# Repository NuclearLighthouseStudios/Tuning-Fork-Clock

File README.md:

# Tuning Fork Clock

This repository contains all the files for the Tuning Fork Clock PCB and 3D printed parts.

The PCB was designed for home etching, so the traces are very wide and
the via dimater has been increased so wires can be soldered in to make connections between the layers.

All external connections are broken out on an edge connector at the top that serves as solder pads for making connections.

The "fork mount" directory contains the CAD and STL files for the tuning fork mounting hardware.  
Two 22mH inductors and a 15x5mm neodymium magnet need to be inserted into the base part of the mount.

The polarity of the inductors is not consistent from the factory, so some experimentation is required to get the best results.  
Usually flipping one inductor or the magnet will result in much better vibration of the fork.

The on-board BNC connector can be connected to a scope to observe the output waveform of the pickup.

Check out the [YouTube video](https://www.youtube.com/watch?v=TgB_1jr5b_c) for more info on how it all works.

Also check out [this repository](https://github.com/NuclearLighthouseStudios/Tuning-Fork-Clock-Firmware) for the firmware.

| Reference                                         | Quantity | Value         | Description                                          |
| :------------------------------------------------ | -------: | ------------: | :--------------------------------------------------- |
| C1 C4 C5 C9 C102 C103 C104 C105 C106 C107         | 10       | 100n          | Generic ceramic capacitor                            |
| C101                                              | 1        | 100µ          | Electrolytic capacitor, 16V                          |
| C2 C3                                             | 2        | 47n           | Generic ceramic capacitor                            |
| D1                                                | 1        | 1N4148        | DO-35 Diode                                          |
| D2 D3 D4                                          | 3        |               | 5mm LED                                              |
| J3                                                | 1        |               | Panel Mount BNC Connector                            |
| Q1 Q2 Q3 Q4 Q5 Q6 Q7                              | 7        | BC547B        | 0.1A Ic, 45V Vce, Small Signal NPN Transistor, TO-92 |
| R1 R7 R12 R13 R14 R15 R16 R17 R18 R19 R25 R26 R27 | 13       | 1k            | Metal film resistor 1%, DIN 0207, Horizontal         |
| R2 R6                                             | 2        | 1M            | Metal film resistor 1%, DIN 0207, Horizontal         |
| R20 R21 R22 R23 R24                               | 5        | 10k           | Metal film resistor 1%, DIN 0207, Vertical           |
| R3                                                | 1        | 4.7k          | Metal film resistor 1%, DIN 0207, Horizontal         |
| R4 R5 R10                                         | 3        | 10k           | Metal film resistor 1%, DIN 0207, Horizontal         |
| R8 R9                                             | 2        | 100k          | Metal film resistor 1%, DIN 0207, Horizontal         |
| SW1                                               | 1        |               | Alps EC12E Rotary Encoder with Switch, Vertical      |
| U1                                                | 1        | NE555P        | Precision Timers, 555 compatible, PDIP-8             |
| U10                                               | 1        | 440Hz         | Tuning Fork in 3D printed mount                      |
| U10                                               | 2        | 22mH          | 11mm diameter inductor                               |
| U10                                               | 1        |               | 15x5mm neodymium rod magnet                          |
| U2                                                | 1        | ATtiny4313-PU | 8-Bit Microcontroller, 20Mhz, 4k Flash, 256b RAM     |
| U3                                                | 1        | 74HC595       | 8−Bit shift register                                 |
| U4 U5 U6 U7 U8                                    | 5        | SC39-11YWA    | 7 Segment Display                                    |
| U9                                                | 1        | L7805         | 5V voltage regulator, TO-220                         |

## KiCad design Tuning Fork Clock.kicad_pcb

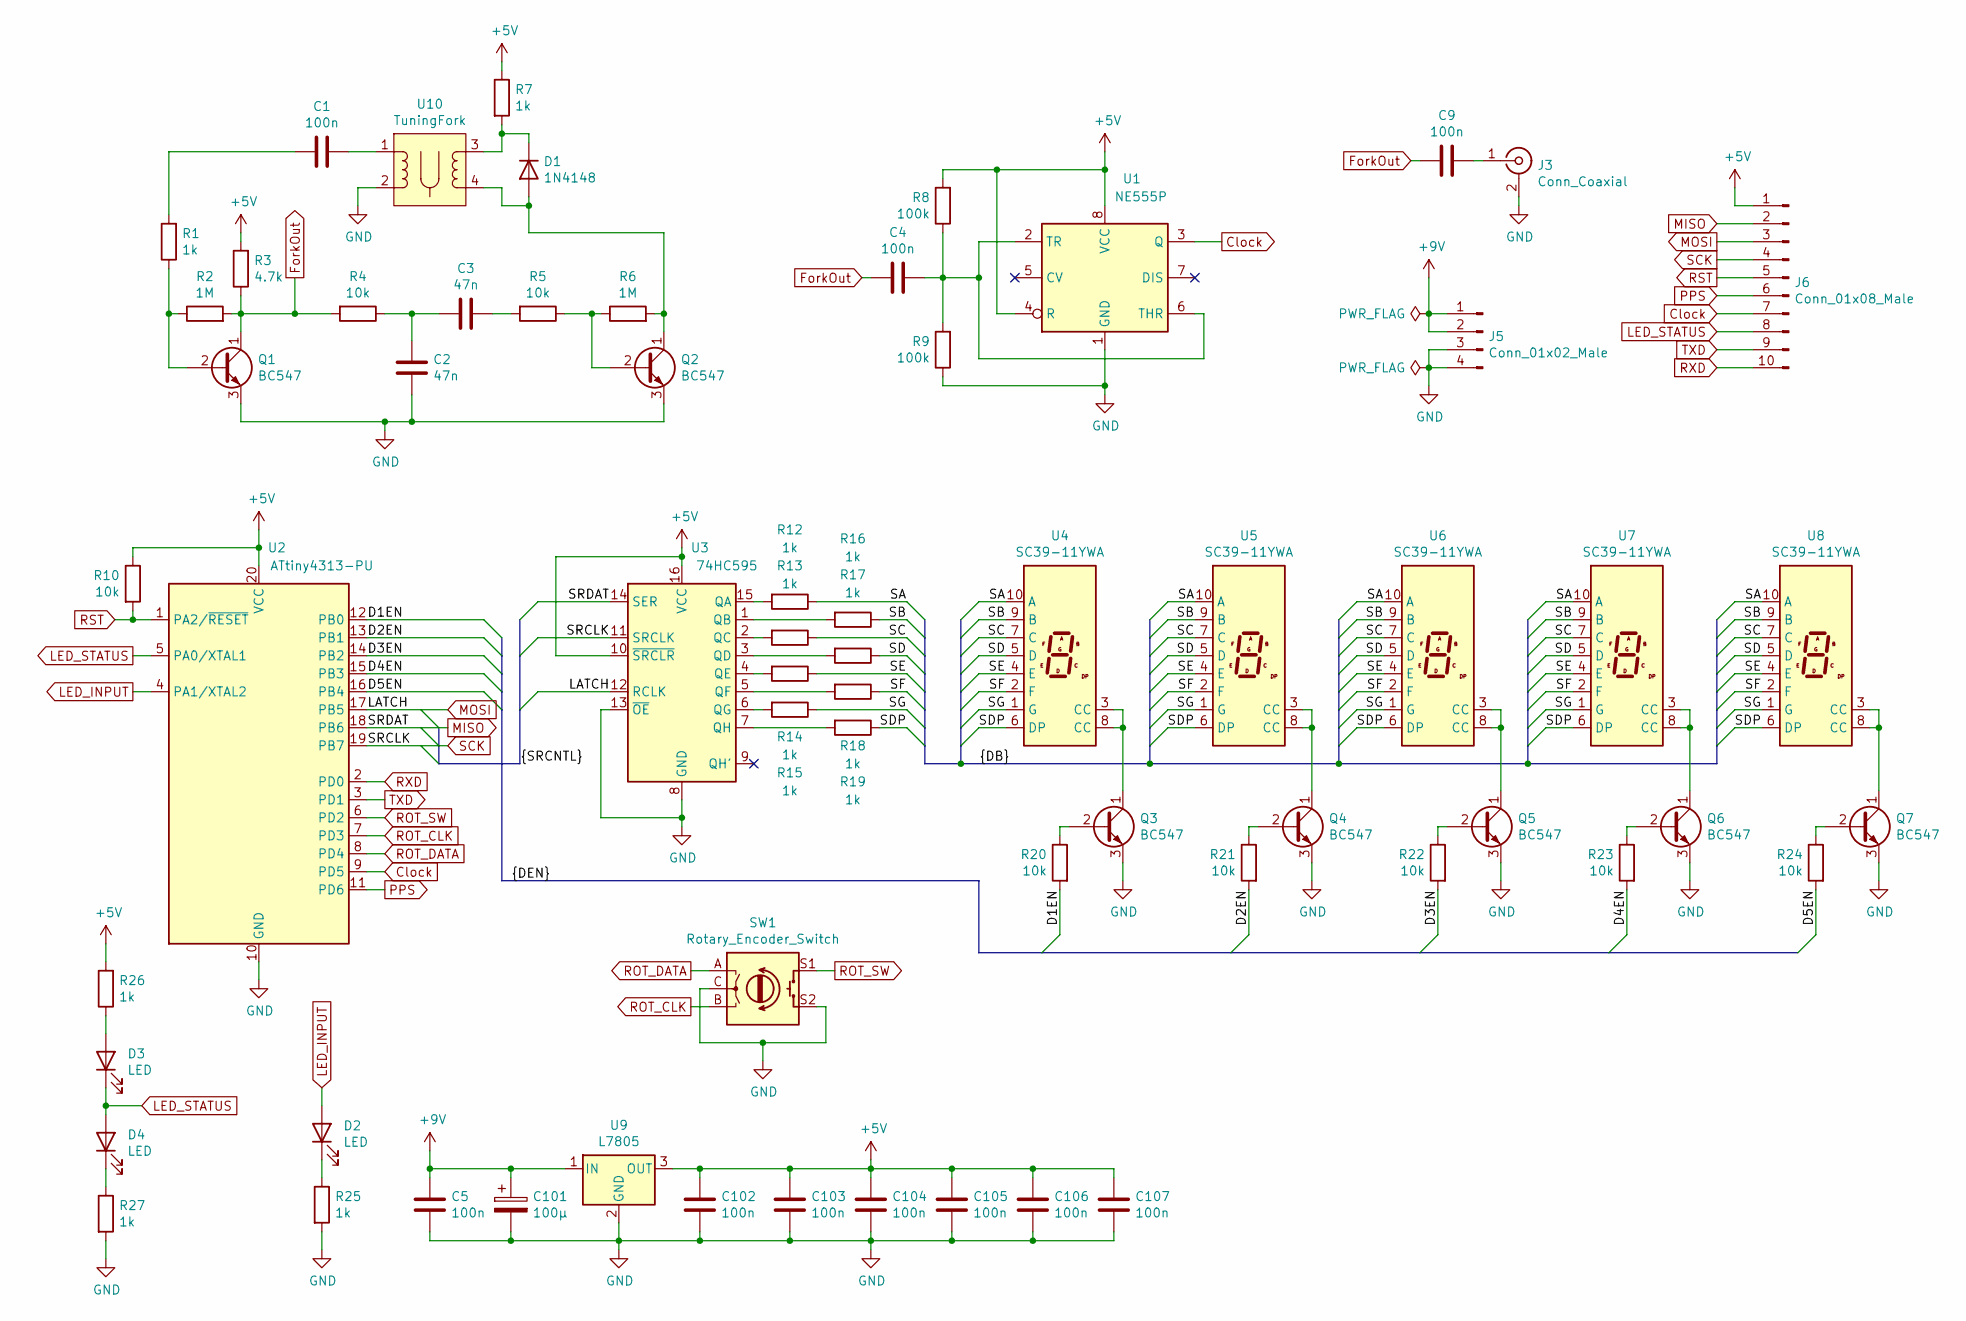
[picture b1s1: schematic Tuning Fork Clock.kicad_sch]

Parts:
C1, C4, C5, C9, C102, C103, C104, C105, C106, C107: 100n; C_Disc_D4.3mm_W1.9mm_P5.00mm
C2, C3: 47n; C_Disc_D4.3mm_W1.9mm_P5.00mm
C101: 100µ; CP_Radial_D6.3mm_P2.50mm
D1: 1N4148; D_DO-35_SOD27_P7.62mm_Horizontal
D2, D3, D4: LED; LED_D5.0mm_Clear
J3: Conn_Coaxial; BNC_PanelMountable_Vertical
J5: Conn_01x02_Male; EdgeConnPower
J6: Conn_01x08_Male; EdgeConnSignal
Q1, Q2, Q3, Q4, Q5, Q6, Q7: BC547; TO-92_Wide
R1, R7, R12, R13, R14, R15, R16, R17, R18, R19, R25, R26, R27: 1k; R_Axial_DIN0207_L6.3mm_D2.5mm_P10.16mm_Horizontal
R2, R6: 1M; R_Axial_DIN0207_L6.3mm_D2.5mm_P10.16mm_Horizontal
R3: 4.7k; R_Axial_DIN0207_L6.3mm_D2.5mm_P10.16mm_Horizontal
R4, R5, R10: 10k; R_Axial_DIN0207_L6.3mm_D2.5mm_P10.16mm_Horizontal
R8, R9: 100k; R_Axial_DIN0207_L6.3mm_D2.5mm_P10.16mm_Horizontal
R20, R21, R22, R23, R24: 10k; R_Axial_DIN0207_L6.3mm_D2.5mm_P2.54mm_Vertical
SW1: Rotary_Encoder_Switch; RotaryEncoder_Alps_EC12E-Switch_Vertical_H20mm_CircularMoun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
U1: NE555P; DIP-8_W7.62mm_Socket
U2: ATtiny4313-PU; DIP-20_W7.62mm_Socket
U3: 74HC595; DIP-16_W7.62mm_Socket
U4, U5, U6, U7, U8: SC39-11YWA; 7SegmentLED_LTS6760_LTS6780
U9: L7805; TO-220-3_Horizontal_TabDown
U10: TuningFork; Tuning Fork

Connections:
+5V: C102.1, C103.1, C104.1, C105.1, C106.1, C107.1, J6.1, R3.2, R7.1, R8.2, R10.1, R26.2, U1.4 (R), U1.8 (VCC), U2.20 (VCC), U3.10 (~SRCLR), U3.16 (VCC), U9.3 (OUT)
+9V: C5.1, C101.1, J5.1, J5.2, U9.1 (IN)
/D1EN: R20.2, U2.12 (PB0)
/D2EN: R21.2, U2.13 (PB1)
/D3EN: R22.2, U2.14 (PB2)
/D4EN: R23.2, U2.15 (PB3)
/D5EN: R24.2, U2.16 (PB4)
/SA: R12.1, U4.10 (A), U5.10 (A), U6.10 (A), U7.10 (A), U8.10 (A)
/SB: R16.1, U4.9 (B), U5.9 (B), U6.9 (B), U7.9 (B), U8.9 (B)
/SC: R13.1, U4.7 (C), U5.7 (C), U6.7 (C), U7.7 (C), U8.7 (C)
/SD: R17.1, U4.5 (D), U5.5 (D), U6.5 (D), U7.5 (D), U8.5 (D)
/SDP: R19.1, U4.6 (DP), U5.6 (DP), U6.6 (DP), U7.6 (DP), U8.6 (DP)
/SE: R14.1, U4.4 (E), U5.4 (E), U6.4 (E), U7.4 (E), U8.4 (E)
/SF: R18.1, U4.2 (F), U5.2 (F), U6.2 (F), U7.2 (F), U8.2 (F)
/SG: R15.1, U4.1 (G), U5.1 (G), U6.1 (G), U7.1 (G), U8.1 (G)
Clock: J6.7, U1.3 (Q), U2.9 (PD5)
ForkOut: C4.2, C9.2, Q1.1 (C), R2.2, R3.1, R4.2
GND: C2.2, C5.2, C101.2, C102.2, C103.2, C104.2, C105.2, C106.2, C107.2, J3.2 (Ext), J5.3, J5.4, Q1.3 (E), Q2.3 (E), Q3.3 (E), Q4.3 (E), Q5.3 (E), Q6.3 (E), Q7.3 (E), R9.1, R25.2, R27.2, SW1.C, SW1.S2, U1.1 (GND), U2.10 (GND), U3.8 (GND), U3.13 (~OE), U9.2 (GND), U10.2
LED_INPUT: D2.2 (A), U2.4 (PA1/XTAL2)
LED_STATUS: D3.1 (K), D4.2 (A), J6.8, U2.5 (PA0/XTAL1)
MISO: J6.2, U2.18 (PB6), U3.14 (SER)
MOSI: J6.3, U2.17 (PB5), U3.12 (RCLK)
unnamed: C1.1, U10.1
unnamed: C1.2, R1.2
unnamed: C2.1, C3.2, R4.1
unnamed: C3.1, R5.2
unnamed: C4.1, R8.1, R9.2, U1.2 (TR), U1.6 (THR)
unnamed: C9.1, J3.1 (In)
unnamed: D1.1 (K), R7.2, U10.3
unnamed: D1.2 (A), Q2.1 (C), R6.2, U10.4
unnamed: D2.1 (K), R25.1
unnamed: D3.2 (A), R26.1
unnamed: D4.1 (K), R27.1
unnamed: Q1.2 (B), R1.1, R2.1
unnamed: Q2.2 (B), R5.1, R6.1
unnamed: Q3.1 (C), U4.3 (CC), U4.8 (CC)
unnamed: Q3.2 (B), R20.1
unnamed: Q4.1 (C), U5.3 (CC), U5.8 (CC)
unnamed: Q4.2 (B), R21.1
unnamed: Q5.1 (C), U6.3 (CC), U6.8 (CC)
unnamed: Q5.2 (B), R22.1
unnamed: Q6.1 (C), U7.3 (CC), U7.8 (CC)
unnamed: Q6.2 (B), R23.1
unnamed: Q7.1 (C), U8.3 (CC), U8.8 (CC)
unnamed: Q7.2 (B), R24.1
unnamed: R12.2, U3.15 (QA)
unnamed: R13.2, U3.2 (QC)
unnamed: R14.2, U3.4 (QE)
unnamed: R15.2, U3.6 (QG)
unnamed: R16.2, U3.1 (QB)
unnamed: R17.2, U3.3 (QD)
unnamed: R18.2, U3.5 (QF)
unnamed: R19.2, U3.7 (QH)
PPS: J6.6, U2.11 (PD6)
ROT_CLK: SW1.B, U2.7 (PD3)
ROT_DATA: SW1.A, U2.8 (PD4)
ROT_SW: SW1.S1, U2.6 (PD2)
RST: J6.5, R10.2, U2.1 (PA2/~RESET)
RXD: J6.10, U2.2 (PD0)
SCK: J6.4, U2.19 (PB7), U3.11 (SRCLK)
TXD: J6.9, U2.3 (PD1)

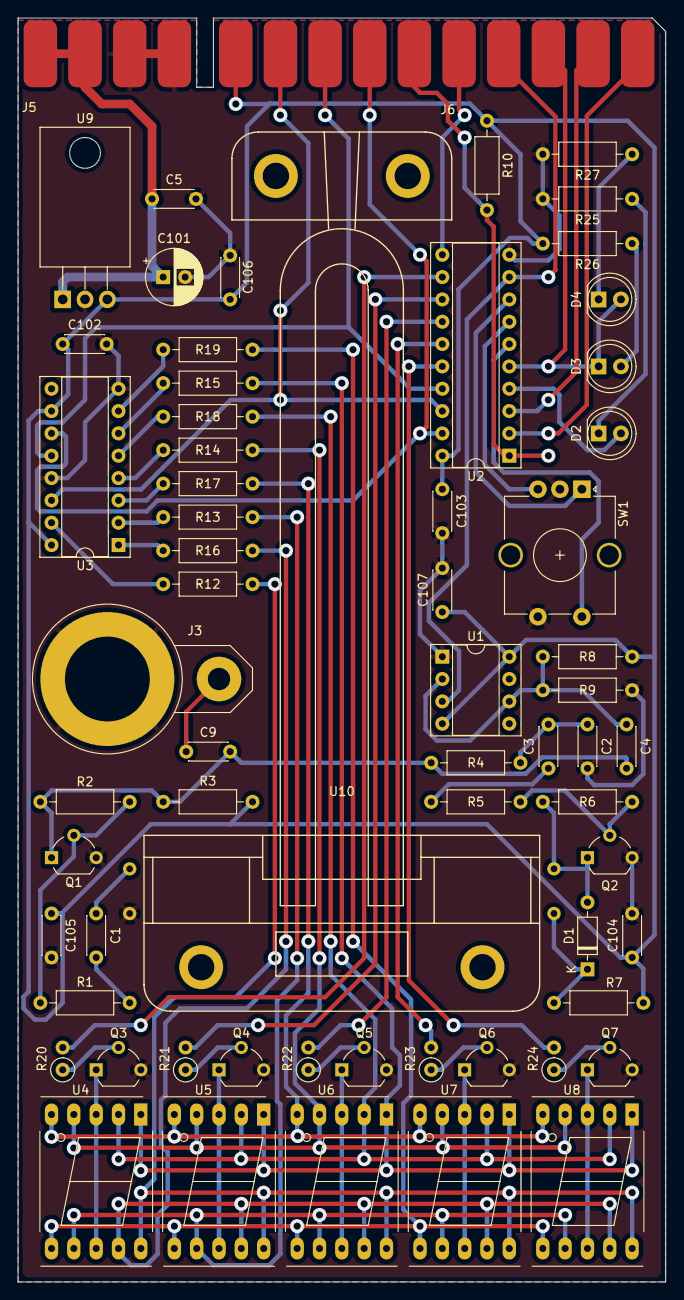
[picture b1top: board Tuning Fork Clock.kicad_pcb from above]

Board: 2 copper layers, 73.7 x 143.8 mm, 64 parts (0 on the bottom side), 61 nets.

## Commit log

2020-05-23 Initial Commit! Yay!
2021-01-30 New README
2021-01-30 Small README tweaks
2022-09-12 Update to KiCAD 6

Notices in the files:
Tuning Fork Clock.kicad_pcb:
CC BY-SA
